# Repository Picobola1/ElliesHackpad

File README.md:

# ElliesHackpad

My insparation to make this was for a friend who loves to play friday night funkin using WASD, and i havent seen her in a while so i though this could be a cool gift.

# BOM:
- 4x Cherry MX Switches
- 4x SK6812 MINI LED
- 1x PCB

  the hardest part about this was my time constraint, the highway end july 31 and i would be a at a over night camp monday through friday that week.... i started this project july 25 lol. i had just about 2 days.

  3d printed parts color: red, keycaps: blue

# PICTURES

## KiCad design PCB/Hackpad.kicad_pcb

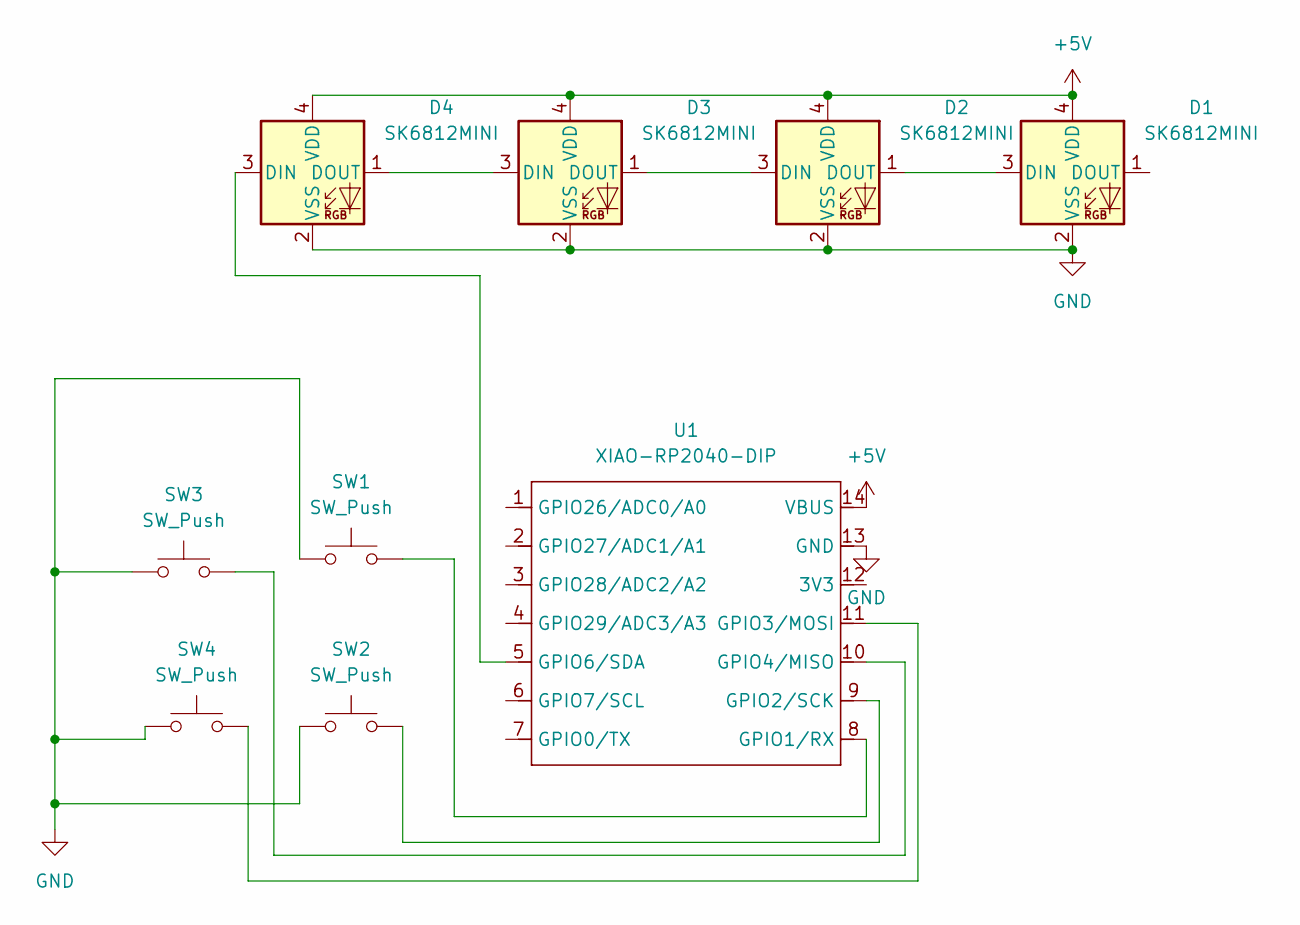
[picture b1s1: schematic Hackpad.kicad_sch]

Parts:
D1, D2, D3, D4: SK6812MINI; LED_SK6812MINI_PLCC4_3.5x3.5mm_P1.75mm
SW1, SW2, SW3, SW4: SW_Push; SW_Cherry_MX_1.00u_PCB
U1: XIAO-RP2040-DIP

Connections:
+5V: D1.4 (VDD), D2.4 (VDD), D3.4 (VDD), D4.4 (VDD), U1.14 (VBUS)
GND: D1.2 (VSS), D2.2 (VSS), D3.2 (VSS), D4.2 (VSS), SW1.1, SW2.1, SW3.1, SW4.1, U1.13 (GND)
unnamed: D1.3 (DIN), D2.1 (DOUT)
unnamed: D2.3 (DIN), D3.1 (DOUT)
unnamed: D3.3 (DIN), D4.1 (DOUT)
unnamed: D4.3 (DIN), U1.5 (GPIO6/SDA)
unnamed: SW1.2, U1.8 (GPIO1/RX)
unnamed: SW2.2, U1.9 (GPIO2/SCK)
unnamed: SW4.2, U1.11 (GPIO3/MOSI)
unnamed: SW3.2, U1.10 (GPIO4/MISO)

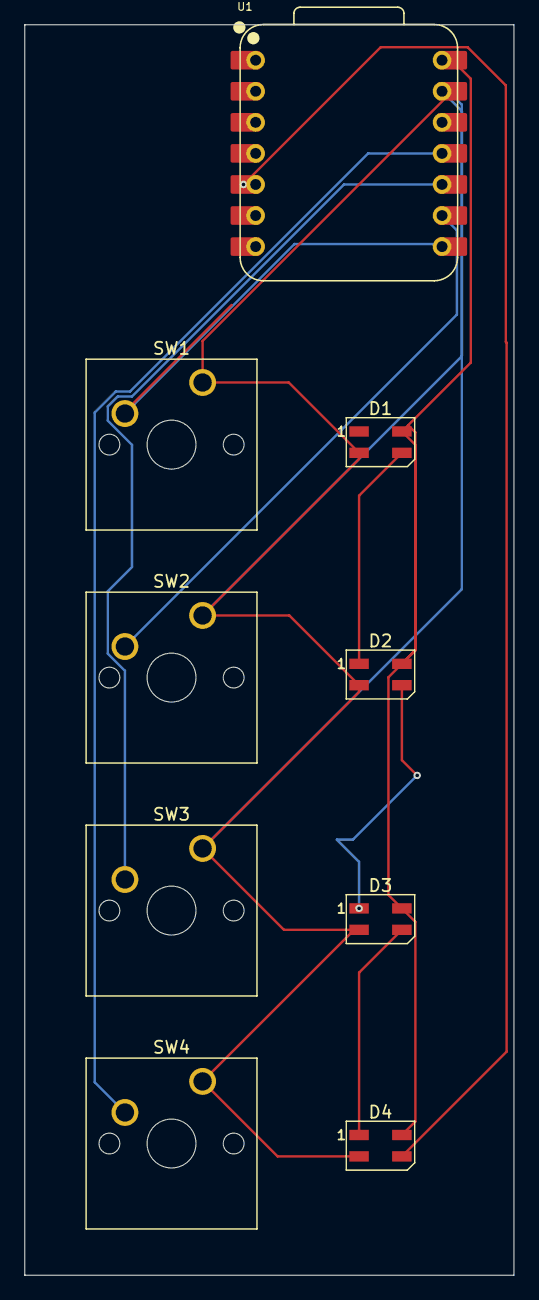
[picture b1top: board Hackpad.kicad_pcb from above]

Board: 2 copper layers, 40.0 x 102.2 mm, 9 parts (0 on the bottom side), 10 nets.

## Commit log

2025-07-26 Create CAD
